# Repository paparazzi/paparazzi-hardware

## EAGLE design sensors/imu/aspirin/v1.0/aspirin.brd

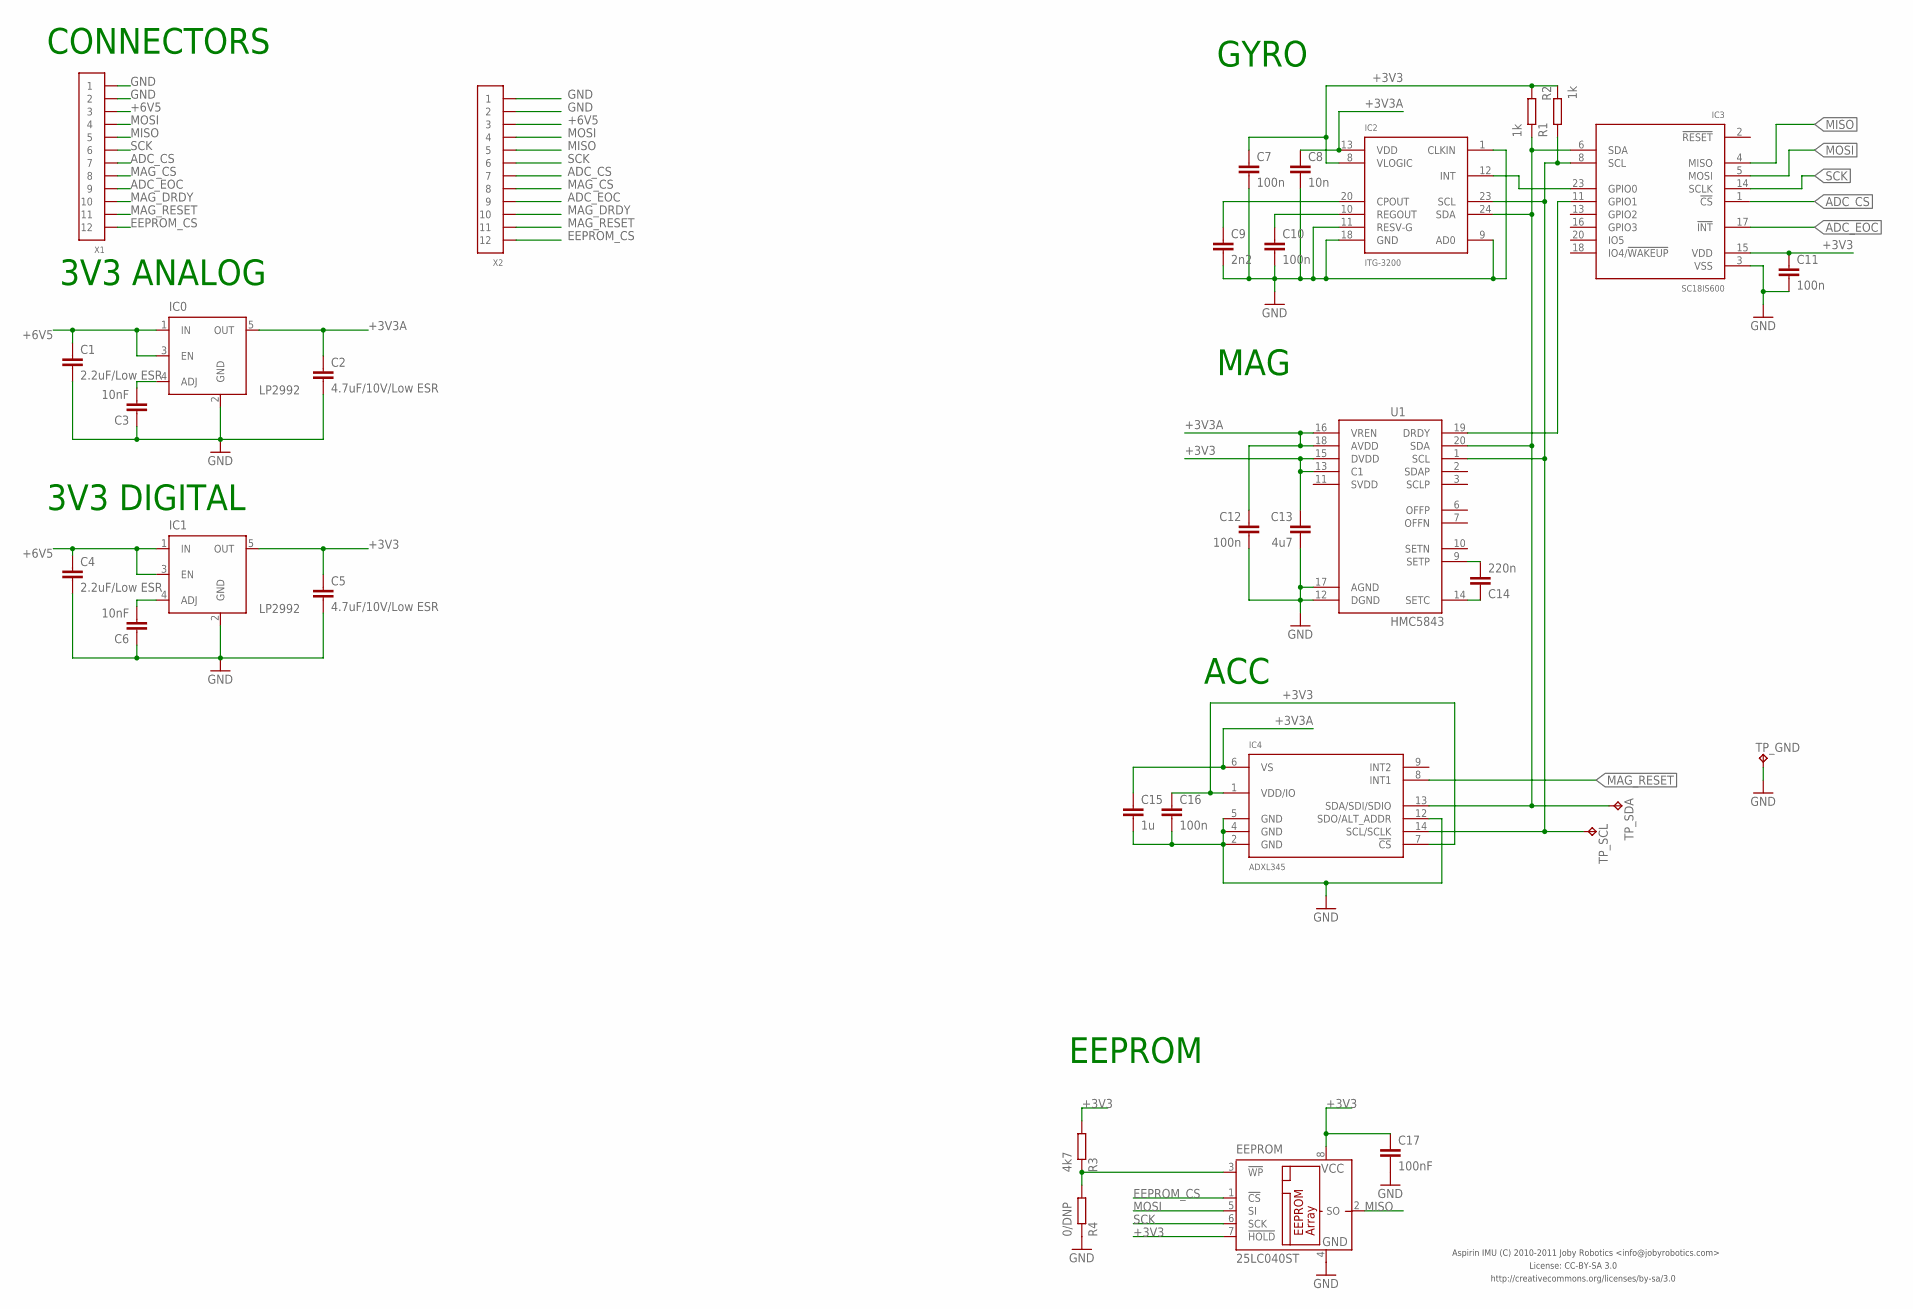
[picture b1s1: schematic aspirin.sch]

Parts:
C1, C4: 2.2uF/Low ESR; 0603-CAP
C2, C5: 4.7uF/10V/Low ESR; 0603-CAP
C3, C6: 10nF; 0603-CAP
C7, C10, C11, C12, C16: 100n; 0603-CAP
C8: 10n; 0603-CAP
C9: 2n2; 0603-CAP
C13: 4u7; 0603-CAP
C14: 220n; 0603-CAP
C15: 1u; 0603-CAP
C17: 100nF; 0603-CAP
EEPROM: 25LC040ST; TSSOP8
IC0, IC1: LP2992; SOT23-5
IC2: ITG-3200; QFN24-WITH-AXES
IC3: SC18IS600; QFN24
IC4: ADXL345; LGA-14
R1, R2: 1k; 0603-RES
R3: 4k7; 0603-RES
R4: 0/DNP; 0603-RES
TP_GND: TP-SMD; MINI_TESTPAD
TP_SCL: TP-SMD; MINI_TESTPAD
TP_SDA: TP-SMD; MINI_TESTPAD
U1: HMC5843; LPCC20-HMC5843
X1: CONN_12-1-53047; PB-53047-12
X2: CONN_12-1-53261; PB-53261-12

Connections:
+3V3: C5.P$1 (1), C7.P$1 (1), C11.P$1 (1), C13.P$1 (1), C16.P$1 (1), C17.P$1 (1), EEPROM.7 (!HOLD), EEPROM.8 (VCC), IC1.5 (OUT), IC2.8 (VLOGIC), IC3.15 (VDD), IC4.1 (VDD/IO), IC4.7 (!CS), R1.P$2 (2), R2.P$1 (1), R3.P$2 (2), U1.13 (C1), U1.15 (DVDD)
+3V3A: C2.P$1 (1), C8.P$1 (1), C12.P$1 (1), C15.P$1 (1), IC0.5 (OUT), IC2.13 (VDD), IC4.6 (VS), U1.16 (VREN), U1.18 (AVDD)
+6V5: C1.P$1 (1), C4.P$1 (1), IC0.1 (IN), IC0.3 (EN), IC1.1 (IN), IC1.3 (EN), X1.3, X2.3
ADC_CS: IC3.1 (!CS), X1.7, X2.7
ADC_EOC: IC3.17 (!INT), X1.9, X2.9
EEPROM_CS: EEPROM.1 (!CS), X1.12, X2.12
GND: C1.P$2 (2), C2.P$2 (2), C3.P$1 (1), C4.P$2 (2), C5.P$2 (2), C6.P$1 (1), C7.P$2 (2), C8.P$2 (2), C9.P$2 (2), C10.P$2 (2), C11.P$2 (2), C12.P$2 (2), C13.P$2 (2), C15.P$2 (2), C16.P$2 (2), C17.P$2 (2), EEPROM.4 (GND), IC0.2 (GND), IC1.2 (GND), IC2.1 (CLKIN), IC2.9 (AD0), IC2.11 (RESV-G), IC2.18 (GND), IC3.3 (VSS), IC4.2 (GND), IC4.4 (GND), IC4.5 (GND), IC4.12 (SDO/ALT_ADDR), R4.P$1 (1), TP_GND.1, U1.12 (DGND), U1.17 (AGND), X1.1, X1.2, X2.1, X2.2
MAG_CS: IC2.12 (INT), IC3.23 (GPIO0), X1.8, X2.8
MAG_DRDY: IC3.11 (GPIO1), U1.19 (DRDY), X1.10, X2.10
MAG_RESET: IC4.8 (INT1), X1.11, X2.11
MISO: EEPROM.2 (SO), IC3.4 (MISO), X1.5, X2.5
MOSI: EEPROM.5 (SI), IC3.5 (MOSI), X1.4, X2.4
unnamed: C9.P$1 (1), IC2.20 (CPOUT)
unnamed: C10.P$1 (1), IC2.10 (REGOUT)
unnamed: C6.P$2 (2), IC1.4 (ADJ)
unnamed: C3.P$2 (2), IC0.4 (ADJ)
unnamed: C14.P$2 (2), U1.9 (SETP)
unnamed: EEPROM.3 (!WP), R3.P$1 (1), R4.P$2 (2)
unnamed: C14.P$1 (1), U1.14 (SETC)
SCK: EEPROM.6 (SCK), IC3.14 (SCLK), X1.6, X2.6
SCL: IC2.23 (SCL), IC3.8 (SCL), IC4.14 (SCL/SCLK), R2.P$2 (2), TP_SCL.1, U1.1 (SCL)
SDA: IC2.24 (SDA), IC3.6 (SDA), IC4.13 (SDA/SDI/SDIO), R1.P$1 (1), TP_SDA.1, U1.20 (SDA)

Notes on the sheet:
3V3 ANALOG
3V3 DIGITAL
CONNECTORS
GYRO
EEPROM
MAG
ACC
License: CC-BY-SA 3.0
http://creativecommons.org/licenses/by-sa/3.0
Aspirin IMU (C) 2010-2011 Joby Robotics <info@jobyrobotics.com>

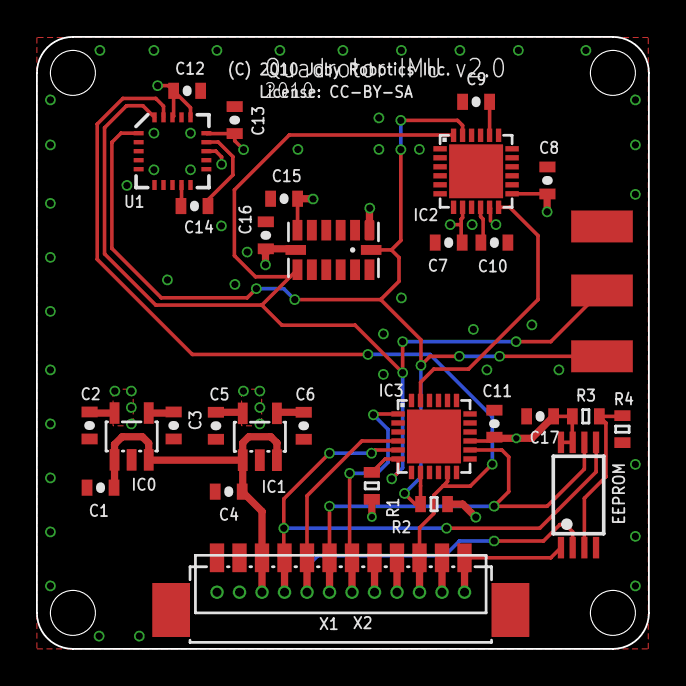
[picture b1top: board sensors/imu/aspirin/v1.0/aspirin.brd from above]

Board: 4 copper layers, 34.0 x 34.0 mm, 33 parts (0 on the bottom side), 22 nets.

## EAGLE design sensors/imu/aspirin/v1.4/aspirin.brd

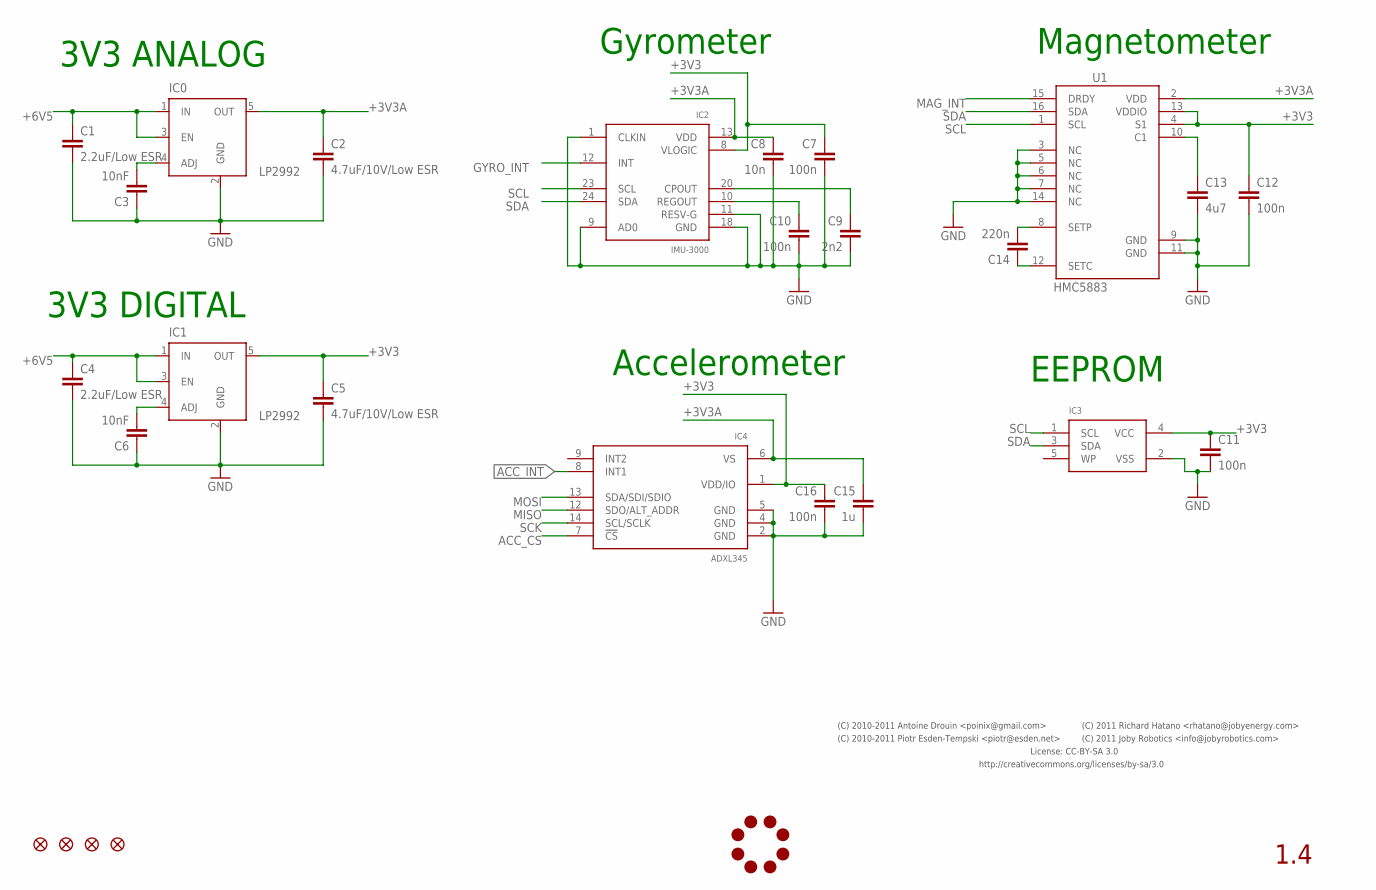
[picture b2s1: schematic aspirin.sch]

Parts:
C1, C4: 2.2uF/Low ESR; 0603-CAP
C2, C5: 4.7uF/10V/Low ESR; 0402-CAP
C3, C6: 10nF; 0402-CAP
C7, C10, C11, C12, C16: 100n; 0402-CAP
C8: 10n; 0402-CAP
C9: 2n2; 0402-CAP
C13: 4u7; 0402-CAP
C14: 220n; 0402-CAP
C15: 1u; 0402-CAP
IC0, IC1: LP2992; SOT23-5
IC2: IMU-3000; QFN24-WITH-AXES
IC3: I2C_EEPROM-SOT23-5; SOT23-5
IC4: ADXL345; LGA-14
JL2: JOBY_LOGO-6MIL; JOBY_LOGO_6MIL
JP1, JP2, JP3, JP4: FIDUCIAL1X2; FIDUCIAL-1X2
U1: HMC5883; PLCC16-HMC5883

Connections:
+3V3: C5.P$1 (1), C7.P$1 (1), C11.P$1 (1), C12.P$1 (1), C16.P$1 (1), IC1.5 (OUT), IC2.8 (VLOGIC), IC3.4 (VCC), IC4.1 (VDD/IO), U1.4 (S1), U1.13 (VDDIO)
+3V3A: C2.P$1 (1), C8.P$1 (1), C15.P$1 (1), IC0.5 (OUT), IC2.13 (VDD), IC4.6 (VS), U1.2 (VDD)
+6V5: C1.P$1 (1), C4.P$1 (1), IC0.1 (IN), IC0.3 (EN), IC1.1 (IN), IC1.3 (EN)
ACC_CS: IC4.7 (!CS)
ACC_INT: IC4.8 (INT1)
GND: C1.P$2 (2), C2.P$2 (2), C3.P$1 (1), C4.P$2 (2), C5.P$2 (2), C6.P$1 (1), C7.P$2 (2), C8.P$2 (2), C9.P$2 (2), C10.P$2 (2), C11.P$2 (2), C12.P$2 (2), C13.P$2 (2), C15.P$2 (2), C16.P$2 (2), IC0.2 (GND), IC1.2 (GND), IC2.1 (CLKIN), IC2.9 (AD0), IC2.11 (RESV-G), IC2.18 (GND), IC3.2 (VSS), IC4.2 (GND), IC4.4 (GND), IC4.5 (GND), U1.3 (NC), U1.5 (NC), U1.6 (NC), U1.7 (NC), U1.9 (GND), U1.11 (GND), U1.14 (NC)
GYRO_INT: IC2.12 (INT)
MAG_INT: U1.15 (DRDY)
MISO: IC4.12 (SDO/ALT_ADDR)
MOSI: IC4.13 (SDA/SDI/SDIO)
unnamed: C9.P$1 (1), IC2.20 (CPOUT)
unnamed: C10.P$1 (1), IC2.10 (REGOUT)
unnamed: C13.P$1 (1), U1.10 (C1)
unnamed: C6.P$2 (2), IC1.4 (ADJ)
unnamed: C3.P$2 (2), IC0.4 (ADJ)
unnamed: C14.P$2 (2), U1.8 (SETP)
unnamed: C14.P$1 (1), U1.12 (SETC)
SCK: IC4.14 (SCL/SCLK)
SCL: IC2.23 (SCL), IC3.1 (SCL), U1.1 (SCL)
SDA: IC2.24 (SDA), IC3.3 (SDA), U1.16 (SDA)

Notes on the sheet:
3V3 ANALOG
3V3 DIGITAL
Gyrometer
EEPROM
Magnetometer
Accelerometer
1.4
License: CC-BY-SA 3.0
http://creativecommons.org/licenses/by-sa/3.0
(C) 2010-2011 Piotr Esden-Tempski <piotr@esden.net>
(C) 2010-2011 Antoine Drouin <poinix@gmail.com>
(C) 2011 Richard Hatano <rhatano@jobyenergy.com>
(C) 2011 Joby Robotics <info@jobyrobotics.com>

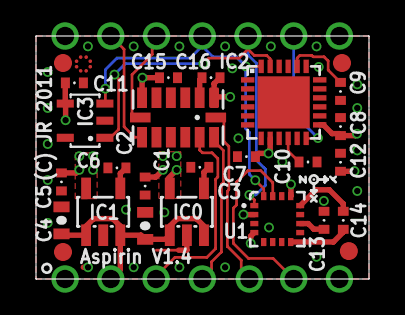
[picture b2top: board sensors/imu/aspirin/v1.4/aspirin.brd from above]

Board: 4 copper layers, 18.5 x 13.5 mm, 28 parts (0 on the bottom side), 13 nets.

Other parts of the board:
DRILEGEND: DRILEGEND

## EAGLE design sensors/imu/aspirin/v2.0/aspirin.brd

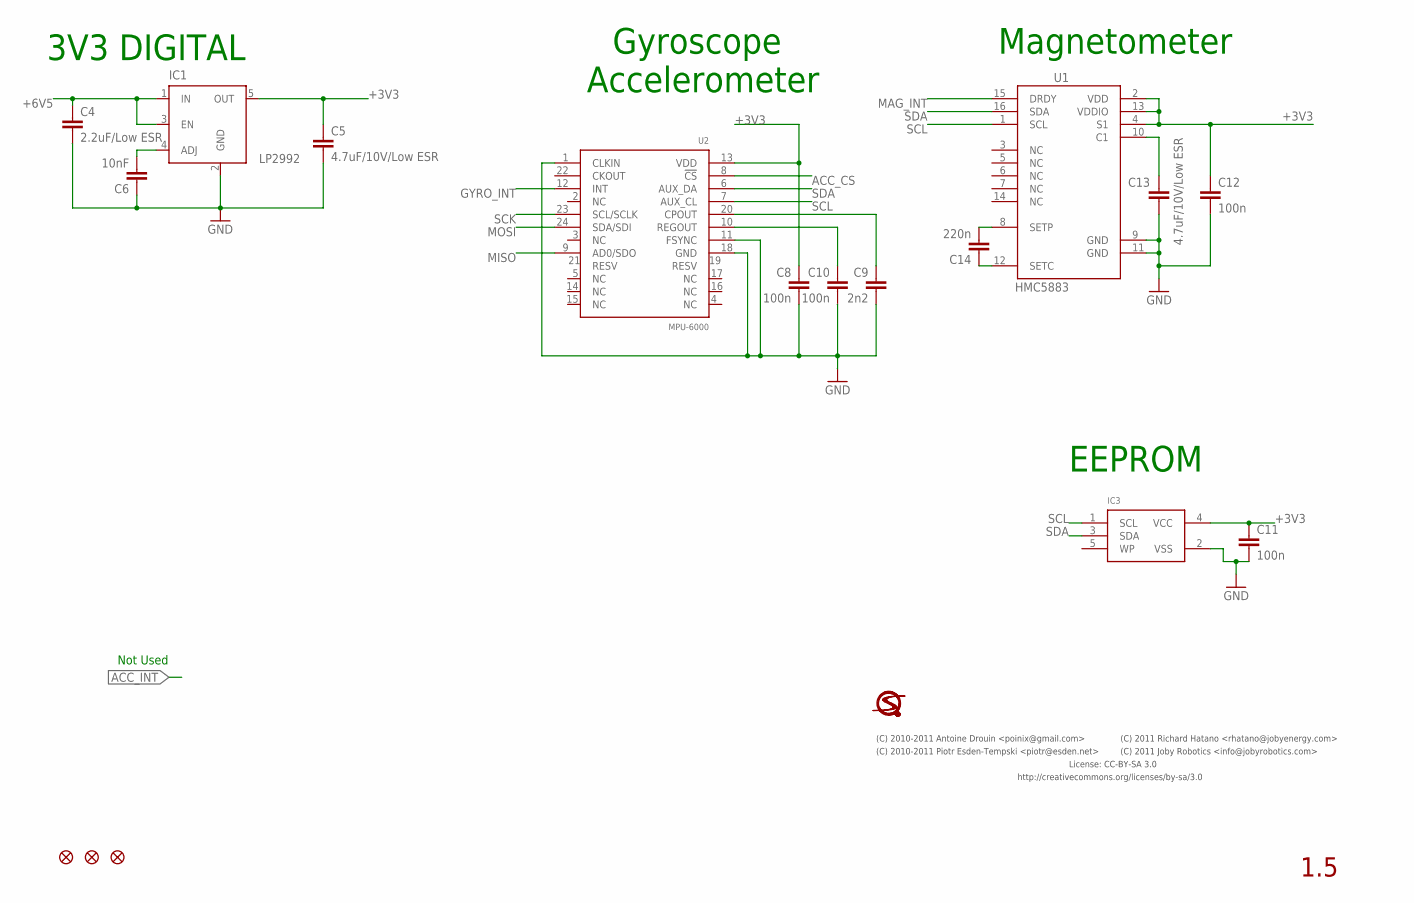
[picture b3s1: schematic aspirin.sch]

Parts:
C4: 2.2uF/Low ESR; 0603-CAP
C5, C13: 4.7uF/10V/Low ESR; 0402-CAP
C6: 10nF; 0402-CAP
C8, C10, C11, C12: 100n; 0402-CAP
C9: 2n2; 0402-CAP
C14: 220n; 0402-CAP
IC1: LP2992; SOT23-5
IC3: I2C_EEPROM-SOT23-5; SOT23-5
JP1, JP2, JP3: FIDUCIAL1X2; FIDUCIAL-1X2
U1: HMC5883; PLCC16-HMC5883
U2: MPU-6000; QFN24-NO-PAD
U$2: LOGO

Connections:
+3V3: C5.P$1 (1), C8.P$1 (1), C11.P$1 (1), C12.P$1 (1), IC1.5 (OUT), IC3.4 (VCC), U1.2 (VDD), U1.4 (S1), U1.13 (VDDIO), U2.13 (VDD)
+6V5: C4.P$1 (1), IC1.1 (IN), IC1.3 (EN)
ACC_CS: U2.8 (!CS)
GND: C4.P$2 (2), C5.P$2 (2), C6.P$1 (1), C8.P$2 (2), C9.P$2 (2), C10.P$2 (2), C11.P$2 (2), C12.P$2 (2), C13.P$2 (2), IC1.2 (GND), IC3.2 (VSS), U1.9 (GND), U1.11 (GND), U2.1 (CLKIN), U2.11 (FSYNC), U2.18 (GND)
GYRO_INT: U2.12 (INT)
MAG_INT: U1.15 (DRDY)
MISO: U2.9 (AD0/SDO)
MOSI: U2.24 (SDA/SDI)
unnamed: C9.P$1 (1), U2.20 (CPOUT)
unnamed: C10.P$1 (1), U2.10 (REGOUT)
unnamed: C13.P$1 (1), U1.10 (C1)
unnamed: C6.P$2 (2), IC1.4 (ADJ)
unnamed: C14.P$2 (2), U1.8 (SETP)
unnamed: C14.P$1 (1), U1.12 (SETC)
SCK: U2.23 (SCL/SCLK)
SCL: IC3.1 (SCL), U1.1 (SCL), U2.7 (AUX_CL)
SDA: IC3.3 (SDA), U1.16 (SDA), U2.6 (AUX_DA)

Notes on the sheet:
3V3 DIGITAL
Gyroscope
EEPROM
Magnetometer
Accelerometer
1.5
License: CC-BY-SA 3.0
http://creativecommons.org/licenses/by-sa/3.0
(C) 2010-2011 Piotr Esden-Tempski <piotr@esden.net>
(C) 2010-2011 Antoine Drouin <poinix@gmail.com>
(C) 2011 Richard Hatano <rhatano@jobyenergy.com>
(C) 2011 Joby Robotics <info@jobyrobotics.com>
Not Used

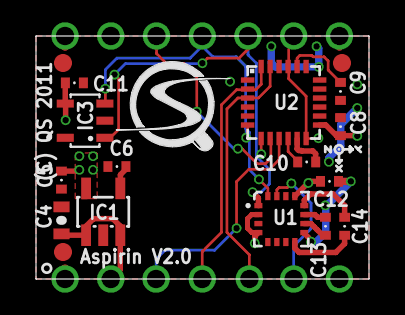
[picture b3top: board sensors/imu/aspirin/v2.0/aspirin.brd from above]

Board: 4 copper layers, 18.5 x 13.5 mm, 19 parts (0 on the bottom side), 11 nets.

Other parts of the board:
DRILEGEND: DRILEGEND

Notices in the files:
sensors/imu/aspirin/v2.2/aspirin.sch:
(C) 2011 Transition Robotics
